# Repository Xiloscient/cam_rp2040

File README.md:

# cam_rp2040
Embedded platform to run basic ml models

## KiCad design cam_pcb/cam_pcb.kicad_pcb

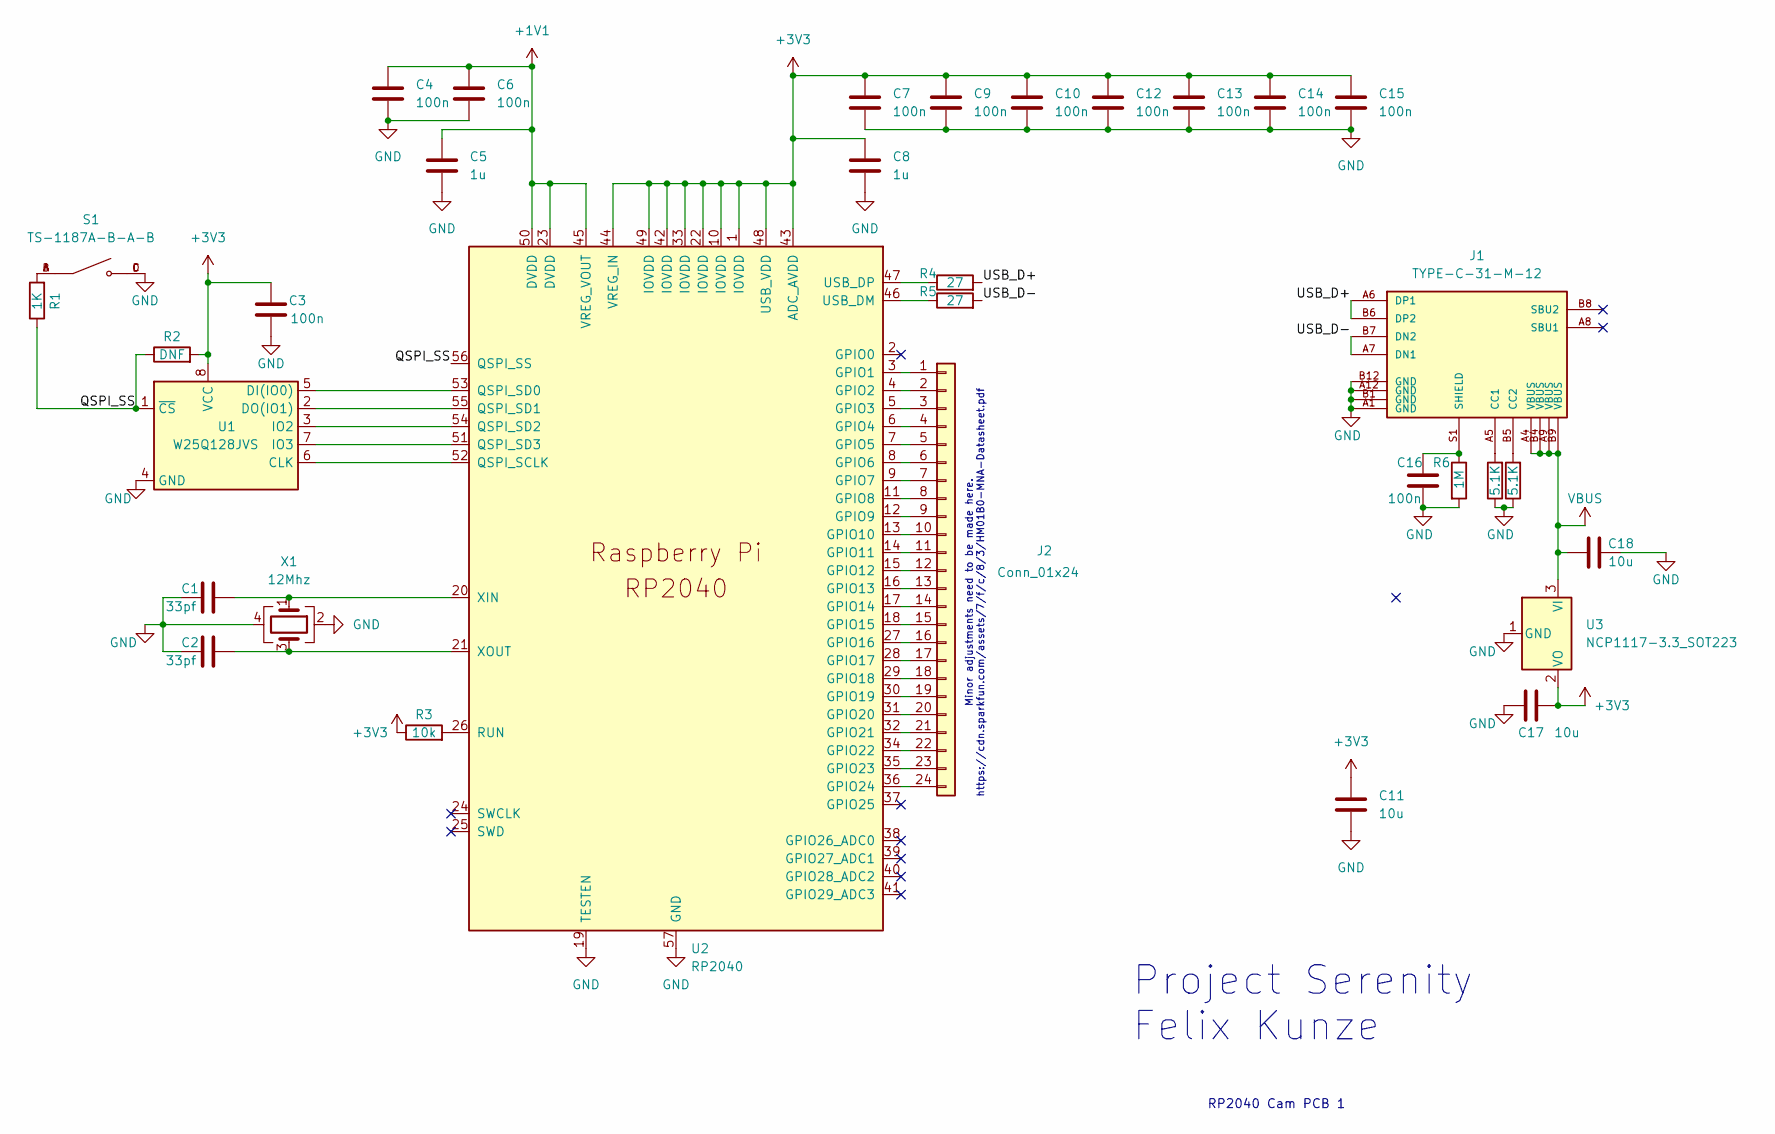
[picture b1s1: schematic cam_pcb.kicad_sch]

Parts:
C1, C2: 33pf; C_0402_1005Metric; LCSC Part # C1562
C3, C4, C6, C7, C9, C10, C12, C13, C14, C15: 100n; C_0402_1005Metric; LCSC Part # C1525
C5, C8: 1u; C_0402_1005Metric; LCSC Part # C52923
C11, C17, C18: 10u; C_0402_1005Metric; LCSC Part # C15525
C16: 100n; C_0603_1608Metric; LCSC Part # C14663
J1: TYPE-C-31-M-12; USB_C_Receptacle_HRO_TYPE-C-31-M-12; PARTREV A; LCSC Part # C165948
J2: Conn_01x24; AMPHENOL_SFV24R-2STE1HLF
R1: 1K; R_0402_1005Metric; LCSC Part # C11702
R2: DNF; R_0402_1005Metric
R3: 10k; R_0402_1005Metric; LCSC Part # C25744
R4, R5: 27; R_0603_1608Metric; LCSC Part # C25190
R6: 1M; R_0603_1608Metric; LCSC Part # C22935
R7, R8: 5.1K; R_0402_1005Metric; LCSC Part # C25905
S1: TS-1187A-B-A-B; SW_TS-1187A-B-A-B; PARTREV A0; LCSC Part # C318884
U1: W25Q128JVS; SOIC-8_5.23x5.23mm_P1.27mm; LCSC Part # C97521
U2: RP2040; RP2040-QFN-56; LCSC Part # C2040
U3: NCP1117-3.3_SOT223; SOT-223-3_TabPin2; LCSC Part # C26537
X1: 12Mhz; Crystal_SMD_3225-4Pin_3.2x2.5mm; LCSC Part # C9002

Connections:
+1V1: C4.1, C5.1, C6.1, U2.23 (DVDD), U2.45 (VREG_VOUT), U2.50 (DVDD)
+3V3: C3.1, C7.1, C8.1, C9.1, C10.1, C11.1, C12.1, C13.1, C14.1, C15.1, C17.2, R2.2, R3.1, U1.8 (VCC), U2.1 (IOVDD), U2.10 (IOVDD), U2.22 (IOVDD), U2.33 (IOVDD), U2.42 (IOVDD), U2.43 (ADC_AVDD), U2.44 (VREG_IN), U2.48 (USB_VDD), U2.49 (IOVDD), U3.2 (VO)
/QSPI_SS: R1.1, R2.1, U1.1 (~CS), U2.56 (QSPI_SS)
/USB_D+: J1.A6 (DP1), J1.B6 (DP2), R4.2
/USB_D-: J1.A7 (DN1), J1.B7 (DN2), R5.2
GND: C1.1, C2.2, C3.2, C4.2, C5.2, C6.2, C7.2, C8.2, C9.2, C10.2, C11.2, C12.2, C13.2, C14.2, C15.2, C16.2, C17.1, C18.1, J1.A1 (GND), J1.A12 (GND), J1.B1 (GND), J1.B12 (GND), R6.2, R7.1, R8.1, S1.C, S1.D, U1.4 (GND), U2.19 (TESTEN), U2.57 (GND), U3.1 (GND), X1.2, X1.4
unnamed: J1.A5 (CC1), R7.2
unnamed: J1.B5 (CC2), R8.2
unnamed: C16.1, J1.S1 (SHIELD), R6.1
unnamed: J2.1, U2.3 (GPIO1)
unnamed: J2.2, U2.4 (GPIO2)
unnamed: J2.3, U2.5 (GPIO3)
unnamed: J2.4, U2.6 (GPIO4)
unnamed: J2.5, U2.7 (GPIO5)
unnamed: J2.6, U2.8 (GPIO6)
unnamed: J2.7, U2.9 (GPIO7)
unnamed: J2.8, U2.11 (GPIO8)
unnamed: J2.9, U2.12 (GPIO9)
unnamed: J2.10, U2.13 (GPIO10)
unnamed: J2.11, U2.14 (GPIO11)
unnamed: J2.12, U2.15 (GPIO12)
unnamed: J2.13, U2.16 (GPIO13)
unnamed: J2.14, U2.17 (GPIO14)
unnamed: J2.15, U2.18 (GPIO15)
unnamed: J2.16, U2.27 (GPIO16)
unnamed: J2.17, U2.28 (GPIO17)
unnamed: J2.18, U2.29 (GPIO18)
unnamed: J2.19, U2.30 (GPIO19)
unnamed: J2.20, U2.31 (GPIO20)
unnamed: J2.21, U2.32 (GPIO21)
unnamed: J2.22, U2.34 (GPIO22)
unnamed: J2.23, U2.35 (GPIO23)
unnamed: J2.24, U2.36 (GPIO24)
unnamed: R1.2, S1.A, S1.B
unnamed: U1.6 (CLK), U2.52 (QSPI_SCLK)
unnamed: U1.5 (DI(IO0)), U2.53 (QSPI_SD0)
unnamed: U1.2 (DO(IO1)), U2.55 (QSPI_SD1)
unnamed: U1.3 (IO2), U2.54 (QSPI_SD2)
unnamed: U1.7 (IO3), U2.51 (QSPI_SD3)
unnamed: R3.2, U2.26 (RUN)
unnamed: R5.1, U2.46 (USB_DM)
unnamed: R4.1, U2.47 (USB_DP)
unnamed: C1.2, U2.20 (XIN), X1.1
unnamed: C2.1, U2.21 (XOUT), X1.3
VBUS: C18.2, J1.A4 (VBUS), J1.A9 (VBUS), J1.B4 (VBUS), J1.B9 (VBUS), U3.3 (VI)

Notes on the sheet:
Project Serenity Felix Kunze
Minor adjustments need to be made here. https://cdn.sparkfun.com/assets/7/f/c/8/3/HM01B0-MNA-Datasheet.pdf
RP2040 Cam PCB 1

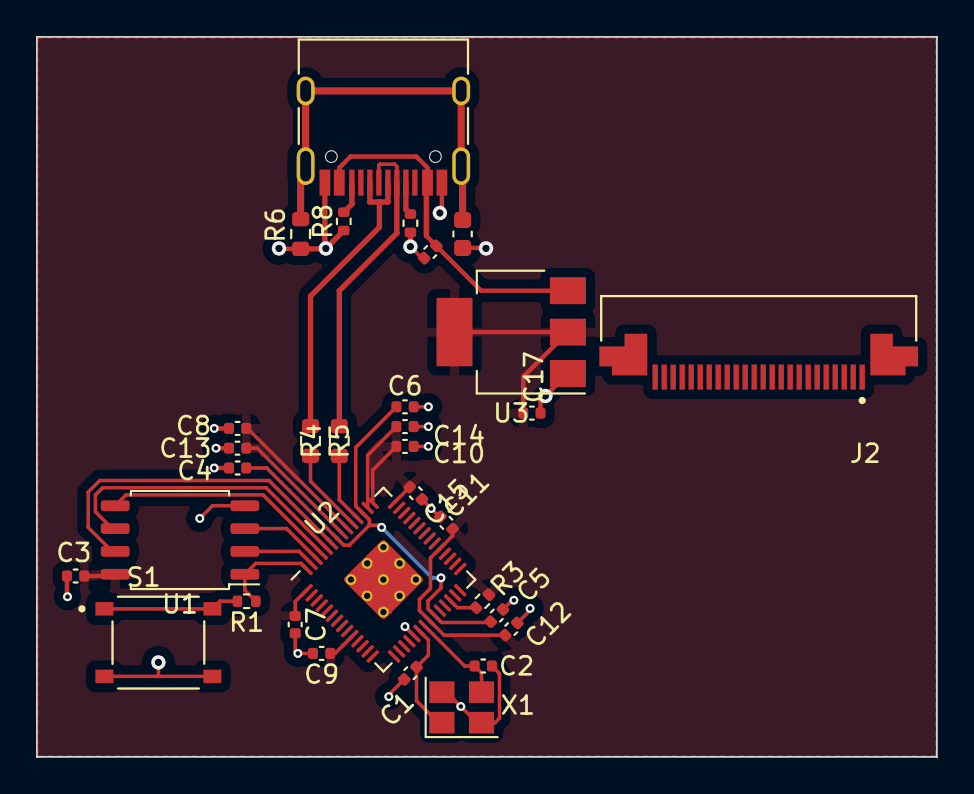
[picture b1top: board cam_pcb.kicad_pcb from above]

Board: 2 copper layers, 50.0 x 40.0 mm, 32 parts (0 on the bottom side), 45 nets.

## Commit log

2024-10-15 added basic pcb
2024-10-15 .DS_Store remove
2024-10-15 images
2024-10-15 all but camera
